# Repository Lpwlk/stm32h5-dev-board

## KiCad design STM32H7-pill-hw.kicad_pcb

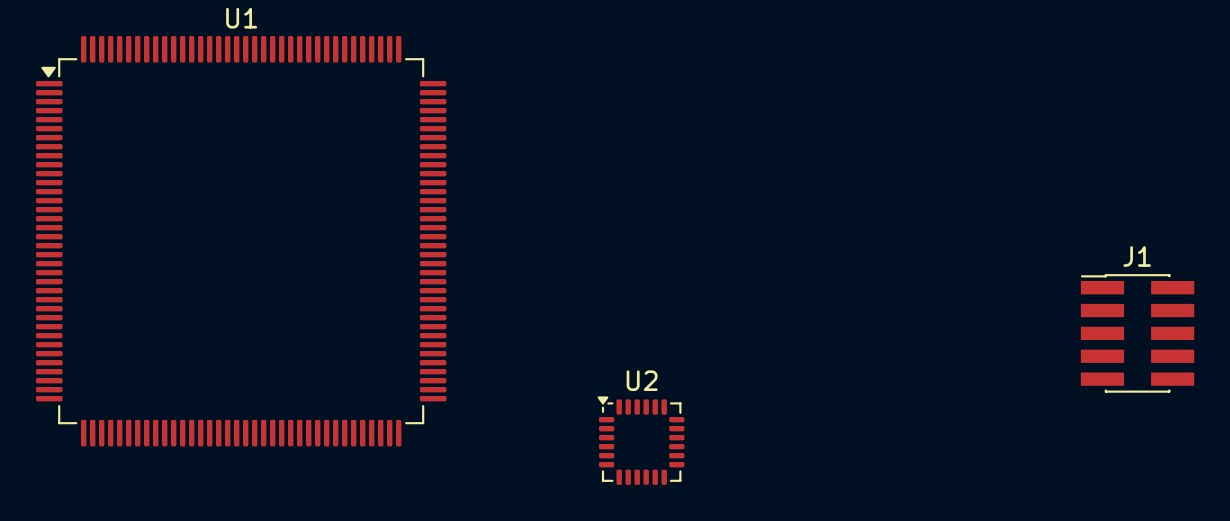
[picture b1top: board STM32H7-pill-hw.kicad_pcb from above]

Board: 2 copper layers, 3 parts (0 on the bottom side), 5 nets, no tracks yet.

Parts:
J1: Conn_ARM_JTAG_SWD_10; PinHeader_2x05_P1.27mm_Vertical_SMD
U1: STM32H573ZITx; LQFP-144_20x20mm_P0.5mm
U2: MPU-6000; InvenSense_QFN-24_4x4mm_P0.5mm

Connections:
/MCU/NRST: J1.10 (~RESET), U1.25 (NRST)
/MCU/SWCLK: J1.4 (SWCLK/TCK), U1.109 (PA14(JTCK)
/MCU/SWDIO: J1.2 (SWDIO/TMS), U1.105 (PA13(JTMS)
GND: J1.3 (GND), J1.5 (GND), J1.9 (GNDDetect), U2.1 (CLKIN), U2.18 (GND)
unnamed: U1.16 (VSS), U1.38 (VSS), U1.51 (VSS), U1.61 (VSS), U1.71 (VSS), U1.83 (VSS), U1.94 (VSS), U1.107 (VSS), U1.120 (VSS), U1.130 (VSS), U1.143 (VSS)
